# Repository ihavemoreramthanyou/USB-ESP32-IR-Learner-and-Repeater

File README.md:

# USB ESP32 IR Learner and Repeater

A USB-powered infrared learning and repeating device based on the ESP32-S3.

The board can receive IR remote-control signals using a Vishay IR receiver, process/store them with the ESP32-S3, and retransmit them using a high-power IR LED driven through a MOSFET.

The board is powered through USB-C and includes native USB data connections to the ESP32-S3 so it can eventually be controlled or configured from a computer.

## Parts:

- ESP32-S3-WROOM-1
- USB-C power and data
- IR receiver
- IR transmitter
- MOSFET-driven IR LED
- Boot and reset buttons
- 5V to 3.3V regulator
- Designed in KiCad

## Current status

PCB V1.0 is fully routed and passes KiCad ERC/DRC aside from a known USB-C footprint hole-clearance issue that will be checked against the PCB manufacturer's fabrication rules.

Firmware is still in development.

## PCB

## How it works

An infrared remote is pointed at the IR receiver on the board.

The receiver demodulates the incoming IR signal and sends the resulting digital signal to the ESP32-S3.

The ESP32 can then analyze or store the received IR data. To retransmit a signal, the ESP32 drives the IR transmitter circuit through a MOSFET, which switches the IR LED.

USB-C provides power as well as a USB connection to the ESP32-S3.

## Project status

- [x] Schematic
- [x] PCB layout
- [x] Routing
- [x] ERC
- [x] DRC cleanup
- [ ] Final BOM
- [ ] Firmware
- [ ] Fabrication files
- [ ] Physical prototype
- [ ] Hardware testing

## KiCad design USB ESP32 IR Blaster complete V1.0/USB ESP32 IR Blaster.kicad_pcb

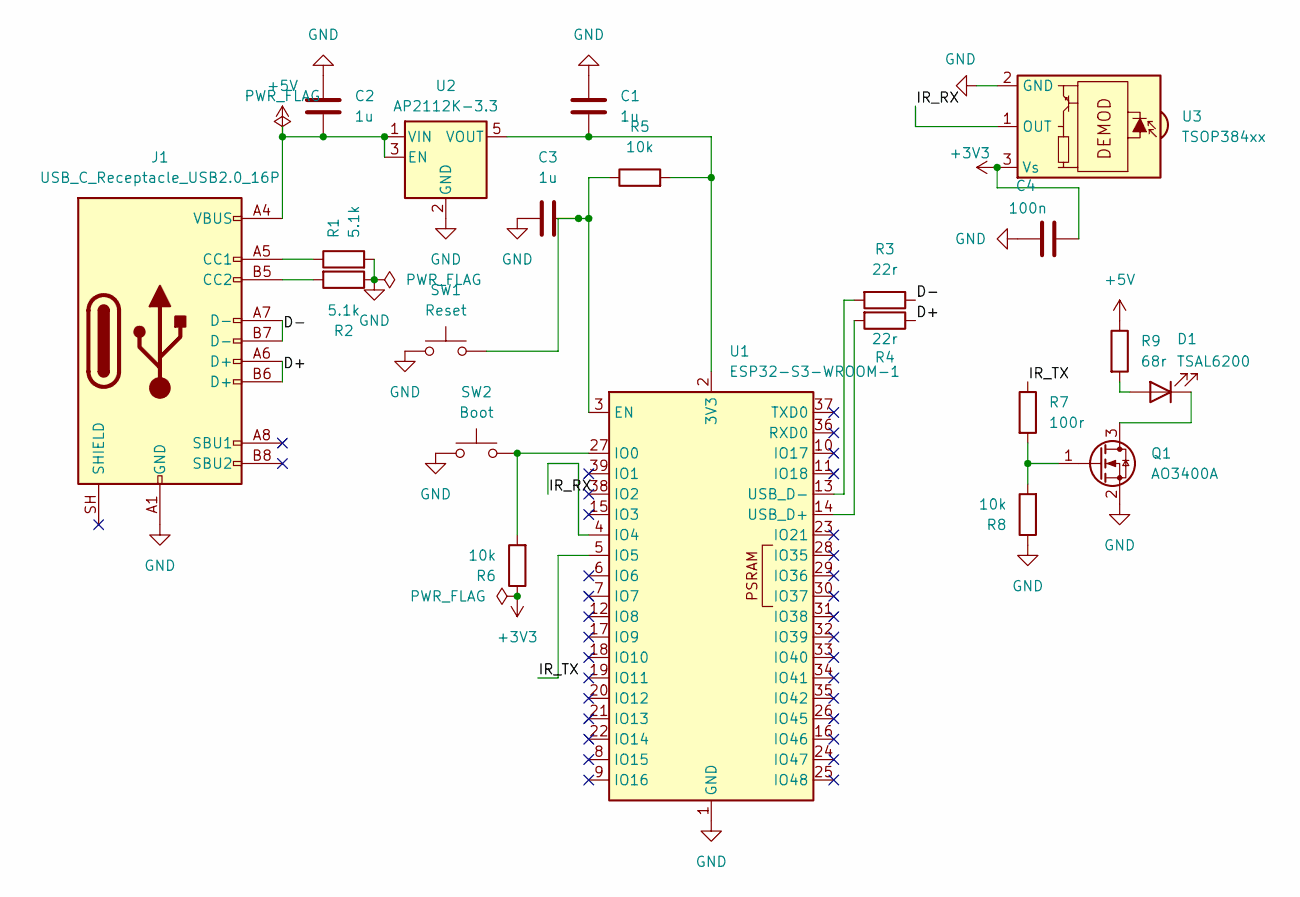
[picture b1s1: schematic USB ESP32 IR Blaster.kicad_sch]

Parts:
C1, C2, C3: 1u; C_0805_2012Metric
C4: 100n; C_0805_2012Metric
D1: TSAL6200; LED_D5.0mm
J1: USB_C_Receptacle_USB2.0_16P; USB_C_Receptacle_GCT_USB4105-xx-A_16P_TopMnt_Horizontal
Q1: AO3400A; SOT-23
R1, R2: 5.1k; R_0805_2012Metric
R3, R4: 22r; R_0805_2012Metric
R5, R6, R8: 10k; R_0805_2012Metric
R7: 100r; R_0805_2012Metric
R9: 68r; R_0805_2012Metric
SW1: Reset; SW_PUSH_6mm
SW2: Boot; SW_PUSH_6mm
U1: ESP32-S3-WROOM-1
U2: AP2112K-3.3; SOT-23-5
U3: TSOP384xx; Vishay_MINICAST-3Pin

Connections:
+3V3: C4.2, R6.1, U3.3 (Vs)
+5V: C2.2, J1.A4 (VBUS), J1.A9 (VBUS), J1.B4 (VBUS), J1.B9 (VBUS), R9.1, U2.1 (VIN), U2.3 (EN)
/D+: J1.A6 (D+), J1.B6 (D+), R4.1
/D-: J1.A7 (D-), J1.B7 (D-), R3.1
/IR_RX: U1.4 (IO4), U3.1 (OUT)
/IR_TX: R7.1, U1.5 (IO5)
GND: C1.1, C2.1, C3.1, C4.1, J1.A1 (GND), J1.A12 (GND), J1.B1 (GND), J1.B12 (GND), Q1.2 (S), R1.2, R2.1, R8.1, SW1.1, SW2.1, U1.1 (GND), U1.40 (GND), U1.41 (GND), U2.2 (GND), U3.2 (GND)
unnamed: D1.2 (A), R9.2
unnamed: D1.1 (K), Q1.3 (D)
unnamed: J1.A5 (CC1), R1.1
unnamed: J1.B5 (CC2), R2.2
unnamed: Q1.1 (G), R7.2, R8.2
unnamed: C1.2, R5.2, U1.2 (3V3), U2.5 (VOUT)
unnamed: C3.2, R5.1, SW1.2, U1.3 (EN)
unnamed: R6.2, SW2.2, U1.27 (IO0)
unnamed: R4.2, U1.14 (USB_D+)
unnamed: R3.2, U1.13 (USB_D-)

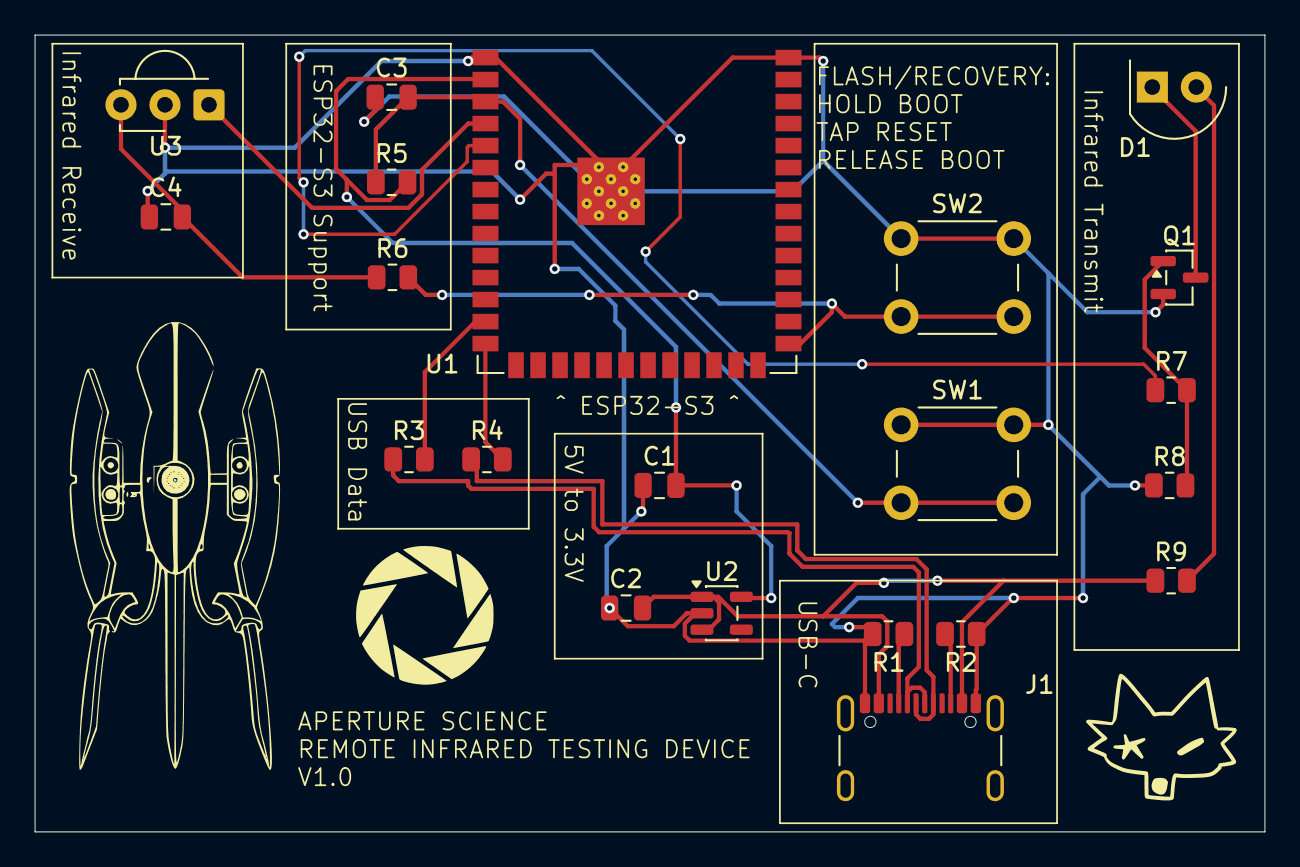
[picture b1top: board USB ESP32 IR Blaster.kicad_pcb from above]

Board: 2 copper layers, 71.0 x 46.0 mm, 21 parts (0 on the bottom side), 17 nets.

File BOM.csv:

"Id";"Designator";"Footprint";"Quantity";"Designation";"Supplier and ref";
1;"C1, C2, C3";"C_0805_2012Metric";3;"1u";;;
2;"C4";"C_0805_2012Metric";1;"100n";;;
3;"D1";"LED_D5.0mm";1;"TSAL6200";;;
4;"J1";"USB_C_Receptacle_GCT_USB4105-xx-A_16P_TopMnt_Horizontal";1;"USB_C_Receptacle_USB2.0_16P";;;
5;"Q1";"SOT-23";1;"AO3400A";;;
6;"R1, R2";"R_0805_2012Metric";2;"5.1k";;;
7;"R3, R4";"R_0805_2012Metric";2;"22r";;;
8;"R5, R6, R8";"R_0805_2012Metric";3;"10k";;;
9;"R7";"R_0805_2012Metric";1;"100r";;;
10;"R9";"R_0805_2012Metric";1;"68r";;;
11;"SW1";"SW_PUSH_6mm";1;"Reset";;;
12;"SW2";"SW_PUSH_6mm";1;"Boot";;;
13;"U1";"ESP32-S3-WROOM-1";1;"ESP32-S3-WROOM-1";;;
14;"U2";"SOT-23-5";1;"AP2112K-3.3";;;
15;"U3";"Vishay_MINICAST-3Pin";1;"TSOP384xx";;;
